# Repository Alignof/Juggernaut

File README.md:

# Juggernaut

Juggernaut は与えられた回路図とプログラムを読み解き，規定内の操作を行うことで時限爆弾型の「装置」を停止させる（解除する）競技です．
解除すべき「装置」とその回路図，書き込まれているプログラムが渡され，その内容を読み解きながらワイヤを切ったりボタンを押したり傾けたりして時間内に「装置」を停止させることを目指します．

作問者には回路構成力とプログラムを柔軟に書く力が，解除する側には回路図やデータシートを読む力とプログラムを素早く間違いなく解読する力が求められ，教育面での効果が期待できます．  
解除するまでの時間を競う競技型や，お互いに装置を作って解除しあってワイワイするイベント型を想定しています．

## 競技規則

[regulation.md](https://github.com/Alignof/Juggernaut/blob/master/regulation.md)を参照．

## 関連リポジトリ

運営などに便利なツールを用意しました．

### [Juggernaut_typst](https://github.com/Alignof/Juggernaut_typst)

運営に提出する仕様書（giver から solver に渡される問題文兼取説）の typst 版テンプレートです．

## 開催履歴

- 2020/12/19: SECCON2020 Contest of Contest 発表
- 2021/10/16: 第1回 SECCONCON 「Juggernaut #000」
- 2023/12/23: Juggernaut #001 @浅草橋ヒューリックホール
- 2024/09/14: Juggernaut #002 @Deep Tech CORE SAPPORO
- 2025/11/12-13: International Cybersecurity Challenge 小中学生向けワークショップ

## Author

2020 10.31  
Norimasa TAKANA  
Homepage: [https://n.takana.dev/](https://n.takana.dev/)  
Github : [https://github.com/Alignof/](https://github.com/Alignof/)  
Twitter : [https://twitter.com/\_Alignof](https://twitter.com/_Alignof)

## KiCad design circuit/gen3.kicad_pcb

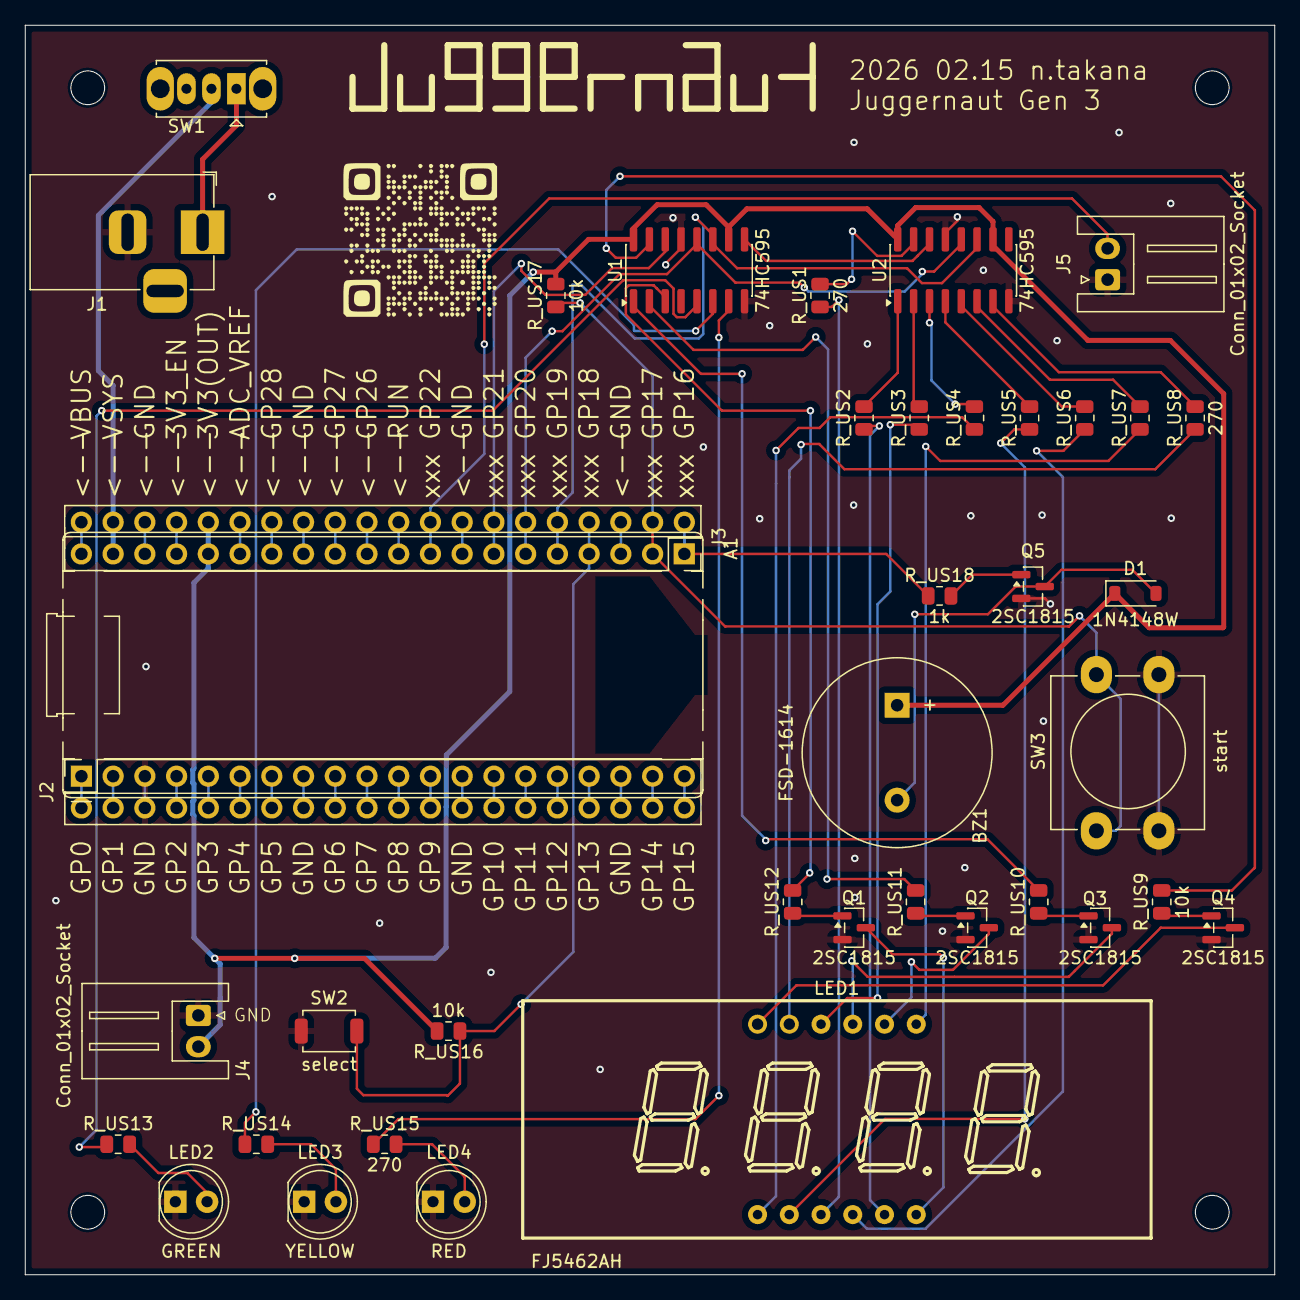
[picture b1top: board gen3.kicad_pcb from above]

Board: 2 copper layers, 100.0 x 100.0 mm, 44 parts (0 on the bottom side), 78 nets.

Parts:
A1: RaspberryPi_Pico; RaspberryPi_Pico_Common_THT
BZ1: FSD-1614; Buzzer_15x7.5RM7.6
D1: 1N4148W; D_SOD-123
H1, H2, H3, H4: MountingHole; MountingHole_2.7mm_M2.5
J1: Jack-DC; BarrelJack_Horizontal
J2: Conn_02x20_Row_Letter_Last; PinSocket_2x20_P2.54mm_1a-20a
J3: Conn_02x20_Row_Letter_Last; PinSocket_2x20_P2.54mm_20a_40a
J4, J5: Conn_01x02_Socket; JST_XH_S2B-XH-A_1x02_P2.50mm_Horizontal
LED1: FJ5462AH
LED2: GREEN; LED_D5.0mm
LED3: YELLOW; LED_D5.0mm
LED4: RED; LED_D5.0mm
Q1, Q2, Q3, Q4, Q5: 2SC1815; SOT-23
R_US1, R_US2, R_US3, R_US4, R_US5, R_US6, R_US7, R_US8, R_US13, R_US14, R_US15: 270; R_0805_2012Metric
R_US9, R_US10, R_US11, R_US12, R_US16, R_US17: 10k; R_0805_2012Metric
R_US18: 1k; R_0805_2012Metric
SW1: SW_Wuerth_450301014042; SW_Slide_SPDT_Straight_CK_OS102011MS2Q
SW2: select; SW_SPST_TS-1088-xR020
SW3: start; SW_PUSH-12mm_Wuerth-430476085716
U1, U2: 74HC595; SOIC-16_3.9x9.9mm_P1.27mm

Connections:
+3V3: BZ1.1 (-), D1.1 (K), J3.36a, J3.36b, J4.2, R_US16.2, R_US17.2, U1.10 (~SRCLR), U1.16 (VCC), U2.10 (~SRCLR), U2.16 (VCC)
/7seg_led/A: LED1.11 (A), R_US8.1
/7seg_led/B: LED1.7 (B), R_US7.1
/7seg_led/C: LED1.4 (C), R_US6.1
/7seg_led/D: LED1.2 (D), R_US5.1
/7seg_led/DIG1: LED1.12 (DIG1), Q4.3 (C)
/7seg_led/DIG2: LED1.9 (DIG2), Q3.3 (C)
/7seg_led/DIG3: LED1.8 (DIG3), Q2.3 (C)
/7seg_led/DIG4: LED1.6 (DIG4), Q1.3 (C)
/7seg_led/DP: LED1.3 (DP), R_US1.1
/7seg_led/E: LED1.1 (E), R_US4.1
/7seg_led/F: LED1.10 (F), R_US3.1
/7seg_led/G: LED1.5 (G), R_US2.1
/Pin1: J2.1a, J2.1b
/Pin2: J2.2a, J2.2b
/Pin4: J2.4a, J2.4b
/Pin5: J2.5a, J2.5b
/Pin6: J2.6a, J2.6b
/Pin7: J2.7a, J2.7b
/Pin8: J2.8a, J2.8b
/Pin9: J2.9a, J2.9b
/Pin10: J2.10a, J2.10b
/Pin11: J2.11a, J2.11b
/Pin12: J2.12a, J2.12b
/Pin13: J2.13a, J2.13b
/Pin14: J2.14a, J2.14b
/Pin15: J2.15a, J2.15b
/Pin16: J2.16a, J2.16b
/Pin17: J2.17a, J2.17b
/Pin18: J2.18a, J2.18b
/Pin19: J2.19a, J2.19b
/Pin20: J2.20a (Pin_none_a), J2.20b (Pin_none_b)
/Pin21: J3.21a, J3.21b, R_US18.1
/Pin22: J3.22a, J3.22b, R_US17.1, SW3.1
/Pin23: J3.23a, J3.23b
/Pin24: J3.24a, J3.24b, R_US16.1, SW2.2
/Pin25: J3.25a, J3.25b, U1.11 (SRCLK), U2.11 (SRCLK)
/Pin26: J3.26a, J3.26b, U1.12 (RCLK), U2.12 (RCLK)
/Pin27: J3.27a, J3.27b, U1.14 (SER)
/Pin28: J3.28a, J3.28b
/Pin29: J3.29a, J3.29b, J5.2
/Pin30: J3.30a, J3.30b
/Pin31: J3.31a, J3.31b
/Pin32: J3.32a, J3.32b
/Pin33: J3.33a, J3.33b
/Pin34: J3.34a, J3.34b
/Pin35: J3.35a, J3.35b
/Pin37: J3.37a, J3.37b
/Pin38: J3.38a, J3.38b
/Pin39: J3.39a, J3.39b, SW1.2 (C)
/Pin40: J3.40a, J3.40b
GNDPWR: J1.2, J2.3a, J2.3b, J4.1, J5.1, LED2.1 (K), LED3.1 (K), LED4.1 (K), Q1.2 (E), Q2.2 (E), Q3.2 (E), Q4.2 (E), Q5.2 (E), SW2.1, SW3.2, U1.8 (GND), U1.13 (~OE), U2.8 (GND), U2.13 (~OE)
unnamed: BZ1.2 (+), D1.2 (A), Q5.3 (C)
unnamed: LED2.2 (A), R_US13.2
unnamed: LED3.2 (A), R_US14.2
unnamed: LED4.2 (A), R_US15.2
unnamed: Q1.1 (B), R_US12.1
unnamed: Q2.1 (B), R_US11.1
unnamed: Q3.1 (B), R_US10.1
unnamed: Q4.1 (B), R_US9.1
unnamed: Q5.1 (B), R_US18.2
unnamed: J1.1, SW1.1 (B)
unnamed: R_US9.2, U1.15 (QA)
unnamed: R_US10.2, U1.1 (QB)
unnamed: R_US11.2, U1.2 (QC)
unnamed: R_US12.2, U1.3 (QD)
unnamed: R_US13.1, U1.5 (QF)
unnamed: R_US14.1, U1.6 (QG)
unnamed: U1.9 (QH'), U2.14 (SER)
unnamed: R_US15.1, U1.7 (QH)
unnamed: R_US1.2, U2.15 (QA)
unnamed: R_US2.2, U2.1 (QB)
unnamed: R_US3.2, U2.2 (QC)
unnamed: R_US4.2, U2.3 (QD)
unnamed: R_US5.2, U2.4 (QE)
unnamed: R_US6.2, U2.5 (QF)
unnamed: R_US7.2, U2.6 (QG)
unnamed: R_US8.2, U2.7 (QH)

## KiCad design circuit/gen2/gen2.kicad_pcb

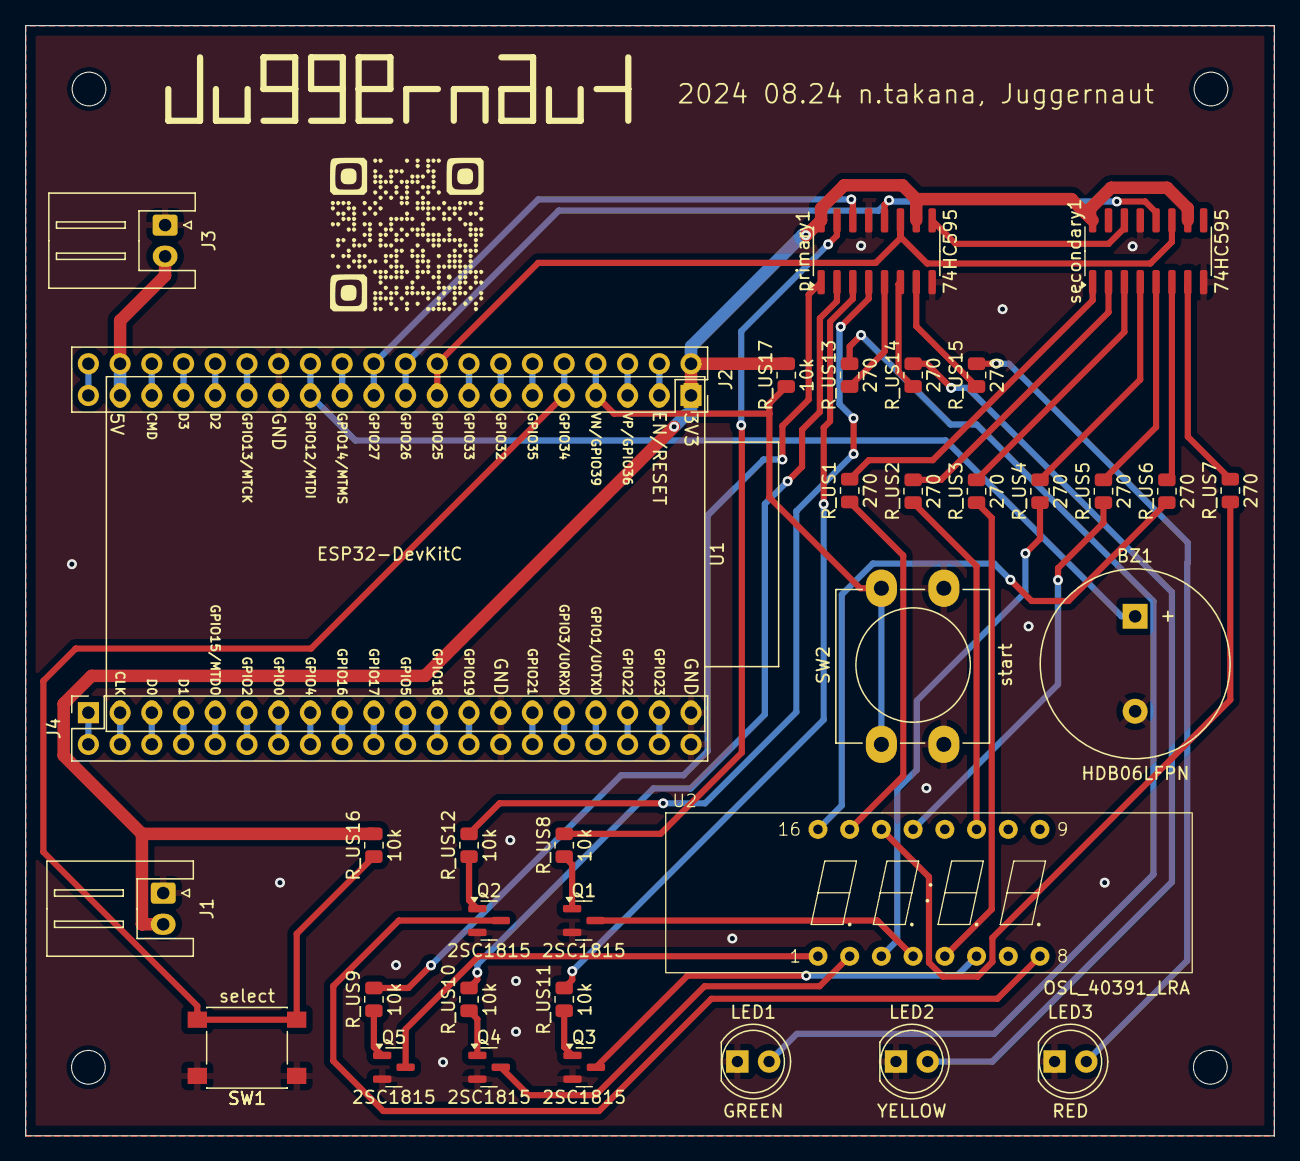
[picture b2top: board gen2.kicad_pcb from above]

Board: 2 copper layers, 100.0 x 88.9 mm, 40 parts (0 on the bottom side), 72 nets.

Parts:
BZ1: HDB06LFPN; Buzzer_15x7.5RM7.6
J1, J3: Conn_01x02_Socket; JST_XH_S2B-XH-A_1x02_P2.50mm_Horizontal
J2: Conn_02x20_Row_Letter_Last; PinSocket_2x20_P2.54mm_1a-19a
J4: Conn_02x20_Row_Letter_Last; PinSocket_2x20_P2.54mm_20a_38a
LED1: GREEN; LED_D5.0mm
LED2: YELLOW; LED_D5.0mm
LED3: RED; LED_D5.0mm
Q1, Q2, Q3, Q4, Q5: 2SC1815; SOT-23
R_US1, R_US2, R_US3, R_US4, R_US5, R_US6, R_US7, R_US13, R_US14, R_US15: 270; R_0805_2012Metric
R_US8, R_US9, R_US10, R_US11, R_US12, R_US16, R_US17: 10k; R_0805_2012Metric
SW1: select; SW_SPST_PTS645
SW2: start; SW_PUSH-12mm_Wuerth-430476085716
U1: ESP32-DevKitC
U2: OSL_40391_LRA
hole_lower_left: MountingHole_2.7mm_M2.5
hole_lower_right: MountingHole_2.7mm_M2.5
hole_upper_left: MountingHole_2.7mm_M2.5
hole_upper_right: MountingHole_2.7mm_M2.5
primary1: 74HC595; SOIC-16_3.9x9.9mm_P1.27mm
secondary1: 74HC595; SOIC-16_3.9x9.9mm_P1.27mm

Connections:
+3V3: J1.2, J2.1a, J2.1b, R_US16.2, R_US17.2, U1.1 (3V3), primary1.10 (~SRCLR), primary1.16 (VCC), secondary1.10 (~SRCLR), secondary1.16 (VCC)
+5V: J2.19a, J2.19b, J3.2, U1.19 (5V)
/Pin2: J2.2a, J2.2b, U1.2 (CHIP_PU)
/Pin3: J2.3a, J2.3b, U1.3 (SENSOR_VP/GPIO36/ADC1_CH0)
/Pin4: J2.4a, J2.4b, R_US17.1, SW2.1, U1.4 (SENSOR_VN/GPIO39/ADC1_CH3)
/Pin5: J2.5a, J2.5b, R_US16.1, SW1.2, U1.5 (VDET_1/GPIO34/ADC1_CH6)
/Pin6: J2.6a, J2.6b, U1.6 (VDET_2/GPIO35/ADC1_CH7)
/Pin7: J2.7a, J2.7b, U1.7 (32K_XP/GPIO32/ADC1_CH4)
/Pin8: J2.8a, J2.8b, U1.8 (32K_XN/GPIO33/ADC1_CH5)
/Pin9: J2.9a, J2.9b, U1.9 (DAC_1/ADC2_CH8/GPIO25), primary1.11 (SRCLK), secondary1.11 (SRCLK)
/Pin10: J2.10a, J2.10b, U1.10 (DAC_2/ADC2_CH9/GPIO26), primary1.12 (RCLK), secondary1.12 (RCLK)
/Pin11: J2.11a, J2.11b, U1.11 (ADC2_CH7/GPIO27), primary1.14 (SER)
/Pin12: J2.12a, J2.12b, U1.12 (MTMS/GPIO14/ADC2_CH6)
/Pin13: BZ1.1 (-), J2.13a, J2.13b, U1.13 (MTDI/GPIO12/ADC2_CH5)
/Pin15: J2.15a, J2.15b, U1.15 (MTCK/GPIO13/ADC2_CH4)
/Pin16: J2.16a, J2.16b, U1.16 (SD_DATA2/GPIO9)
/Pin17: J2.17a, J2.17b, U1.17 (SD_DATA3/GPIO10)
/Pin18: J2.18a, J2.18b, U1.18 (CMD)
/Pin20: J4.20a, J4.20b, U1.20 (SD_CLK/GPIO6)
/Pin21: J4.21a, J4.21b, U1.21 (SD_DATA0/GPIO7)
/Pin22: J4.22a, J4.22b, U1.22 (SD_DATA1/GPIO8)
/Pin23: J4.23a, J4.23b, U1.23 (MTDO/GPIO15/ADC2_CH3)
/Pin24: J4.24a, J4.24b, U1.24 (ADC2_CH2/GPIO2)
/Pin25: J4.25a, J4.25b, U1.25 (GPIO0/BOOT/ADC2_CH1)
/Pin26: J4.26a, J4.26b, U1.26 (ADC2_CH0/GPIO4)
/Pin27: J4.27a, J4.27b, U1.27 (GPIO16)
/Pin28: J4.28a, J4.28b, U1.28 (GPIO17)
/Pin29: J4.29a, J4.29b, U1.29 (GPIO5)
/Pin30: J4.30a, J4.30b, U1.30 (GPIO18)
/Pin31: J4.31a, J4.31b, U1.31 (GPIO19)
/Pin33: J4.33a, J4.33b, U1.33 (GPIO21)
/Pin34: J4.34a, J4.34b, U1.34 (U0RXD/GPIO3)
/Pin35: J4.35a, J4.35b, U1.35 (U0TXD/GPIO1)
/Pin36: J4.36a, J4.36b, U1.36 (GPIO22)
/Pin37: J4.37a, J4.37b, U1.37 (GPIO23)
GNDPWR: BZ1.2 (+), J1.1, J2.14a, J2.14b, J3.1, J4.32a, J4.32b, J4.38a, J4.38b, LED1.1 (K), LED2.1 (K), LED3.1 (K), Q1.2 (E), Q2.2 (E), Q3.2 (E), Q4.2 (E), Q5.2 (E), SW1.1, SW2.2, U1.14 (GND), U1.32 (GND), U1.38 (GND), primary1.8 (GND), primary1.13 (~OE), secondary1.8 (GND), secondary1.13 (~OE)
unnamed: LED1.2 (A), R_US13.2
unnamed: LED2.2 (A), R_US14.2
unnamed: LED3.2 (A), R_US15.2
unnamed: Q1.1 (B), R_US8.1
unnamed: Q1.3 (C), U2.4 (CC5)
unnamed: Q2.1 (B), R_US12.1
unnamed: Q2.3 (C), U2.8 (CC4)
unnamed: Q3.1 (B), R_US11.1
unnamed: Q3.3 (C), U2.6 (CC3)
unnamed: Q4.1 (B), R_US10.1
unnamed: Q4.3 (C), U2.2 (CC2)
unnamed: Q5.1 (B), R_US9.1
unnamed: Q5.3 (C), U2.1 (CC1)
unnamed: R_US7.1, U2.14 (a/D1)
unnamed: R_US6.1, U2.16 (b/D2)
unnamed: R_US5.1, U2.13 (c/D3)
unnamed: R_US4.1, U2.3 (d)
unnamed: R_US3.1, U2.5 (e)
unnamed: R_US2.1, U2.11 (f)
unnamed: R_US1.1, U2.15 (g)
unnamed: R_US8.2, primary1.15 (QA)
unnamed: R_US9.2, primary1.1 (QB)
unnamed: R_US10.2, primary1.2 (QC)
unnamed: R_US11.2, primary1.3 (QD)
unnamed: R_US12.2, primary1.4 (QE)
unnamed: R_US13.1, primary1.5 (QF)
unnamed: R_US14.1, primary1.6 (QG)
unnamed: primary1.9 (QH'), secondary1.14 (SER)
unnamed: R_US15.1, primary1.7 (QH)
unnamed: R_US1.2, secondary1.1 (QB)
unnamed: R_US2.2, secondary1.2 (QC)
unnamed: R_US3.2, secondary1.3 (QD)
unnamed: R_US4.2, secondary1.4 (QE)
unnamed: R_US5.2, secondary1.5 (QF)
unnamed: R_US6.2, secondary1.6 (QG)
unnamed: R_US7.2, secondary1.7 (QH)

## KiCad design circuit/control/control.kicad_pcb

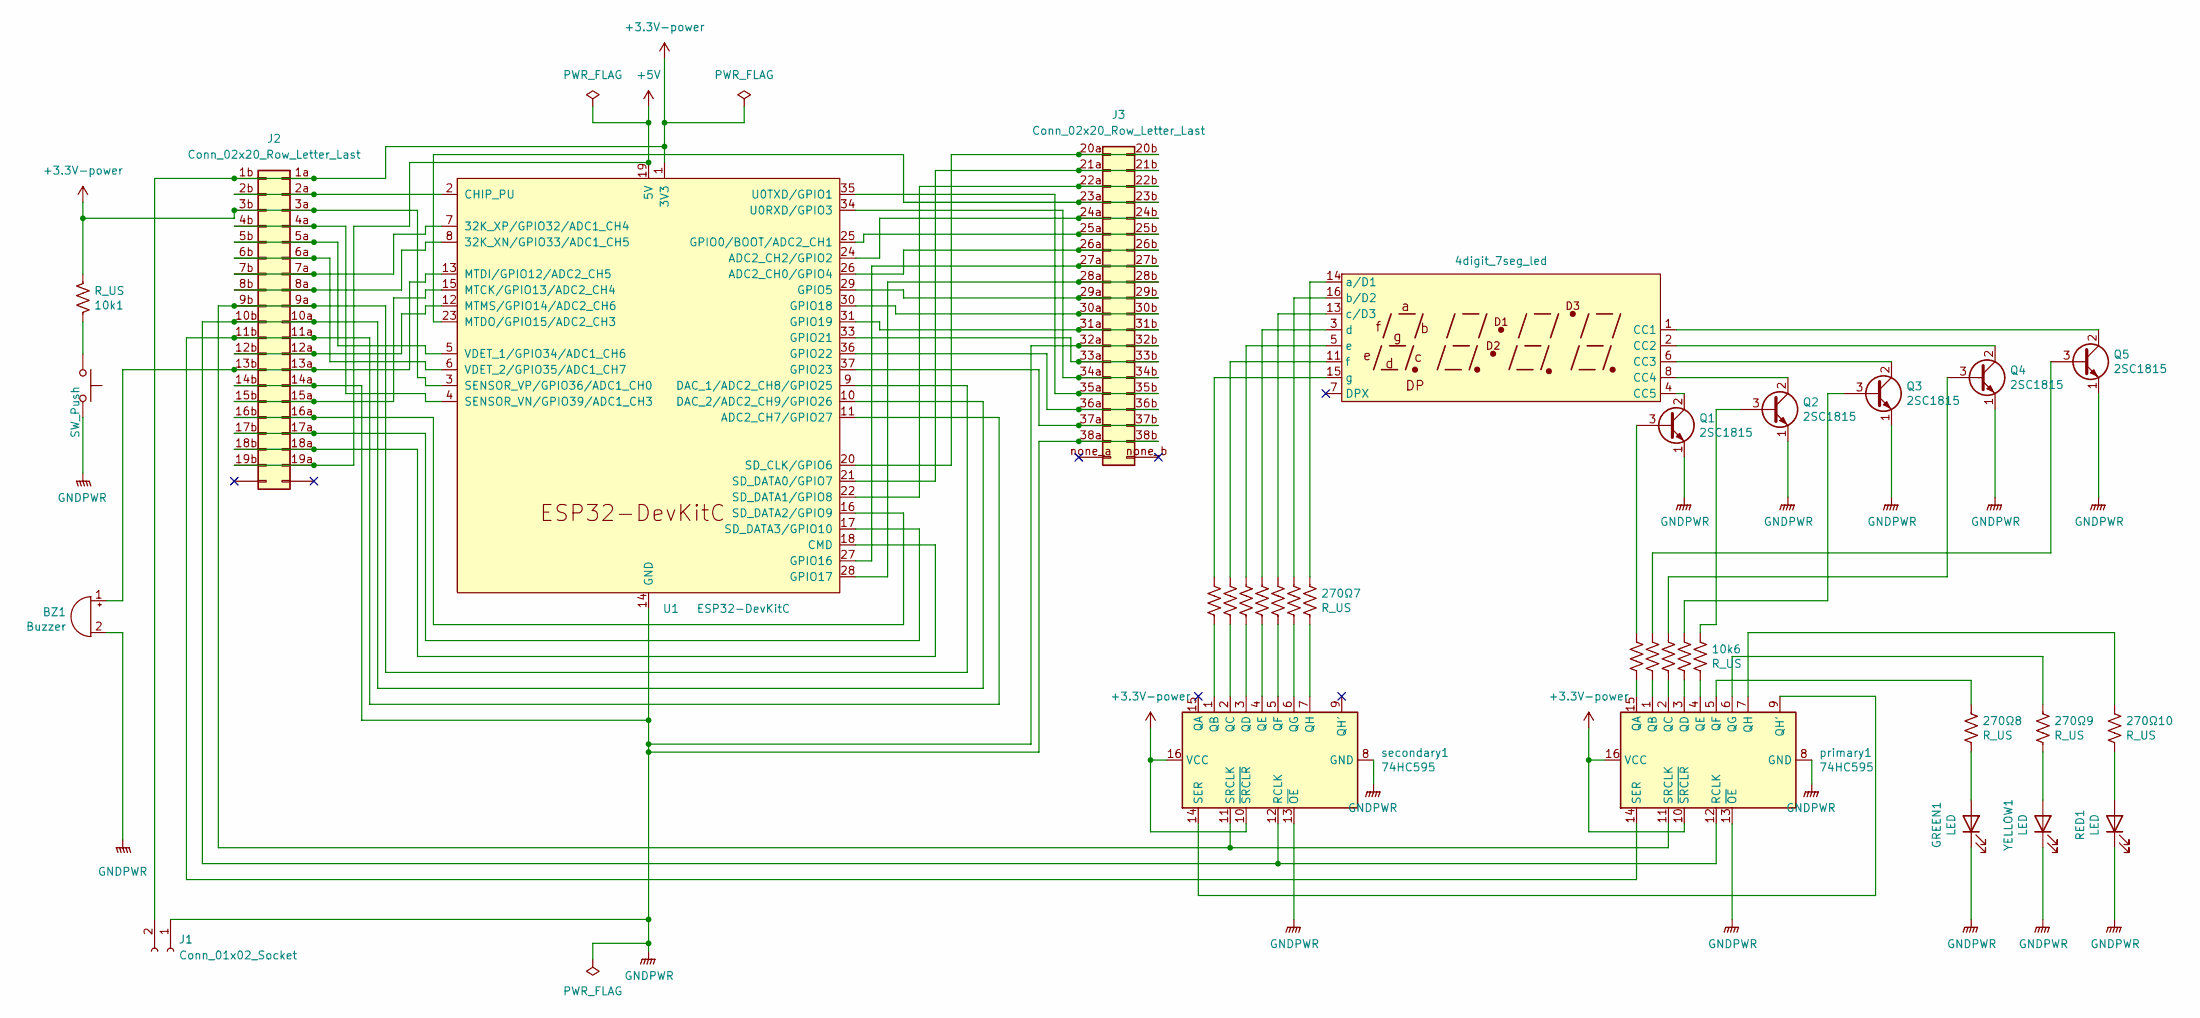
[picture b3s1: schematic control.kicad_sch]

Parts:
10k1, 10k2, 10k3, 10k4, 10k5, 10k6, 270Ω1, 270Ω2, 270Ω3, 270Ω4, 270Ω5, 270Ω6, 270Ω7, 270Ω8, 270Ω9, 270Ω10: R_US; R_Axial_DIN0207_L6.3mm_D2.5mm_P10.16mm_Horizontal
BZ1: Buzzer; Buzzer_15x7.5RM7.6
GREEN1: LED; LED_D1.8mm_W1.8mm_H2.4mm_Horizontal_O1.27mm_Z1.6mm
J1: Conn_01x02_Socket; PinHeader_1x02_P2.54mm_Vertical
J2: Conn_02x20_Row_Letter_Last; PinSocket_2x20_P2.54mm_1a-19a
J3: Conn_02x20_Row_Letter_Last; PinSocket_2x20_P2.54mm_20a_38a
Q1, Q2, Q3, Q4, Q5: 2SC1815; TO-92_Inline_Wide
RED1: LED; LED_D1.8mm_W1.8mm_H2.4mm_Horizontal_O1.27mm_Z1.6mm
SW1: SW_Push; SW_PUSH-12mm_Wuerth-430476085716
U1: ESP32-DevKitC
U2: 4digit_7seg_led; OSL_40391_LRA
YELLOW1: LED; LED_D1.8mm_W1.8mm_H2.4mm_Horizontal_O1.27mm_Z1.6mm
primary1: 74HC595; DIP-16_W7.62mm_Socket
secondary1: 74HC595; DIP-16_W7.62mm_Socket

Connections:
+3V3: 10k1.2, J1.2, J2.1a, J2.1b, J2.3a, J2.3b, U1.1 (3V3), U1.3 (SENSOR_VP/GPIO36/ADC1_CH0), primary1.10 (~SRCLR), primary1.16 (VCC), secondary1.10 (~SRCLR), secondary1.16 (VCC)
+5V: J2.19a, J2.19b, U1.19 (5V)
GNDPWR: BZ1.2 (+), GREEN1.1 (K), J1.1, J2.14a, J2.14b, J3.32a, J3.32b, J3.38a, J3.38b, Q1.1 (E), Q2.1 (E), Q3.1 (E), Q4.1 (E), Q5.1 (E), RED1.1 (K), SW1.1, U1.14 (GND), U1.32 (GND), U1.38 (GND), YELLOW1.1 (K), primary1.8 (GND), primary1.13 (~OE), secondary1.8 (GND), secondary1.13 (~OE); also elsewhere on the board
unnamed: 10k1.1, SW1.2
unnamed 4: BZ1.1 (-), J2.13a, J2.13b, U1.13 (MTDI/GPIO12/ADC2_CH5); also elsewhere on the board
unnamed: 270Ω8.2, GREEN1.2 (A)
unnamed: J2.2a, J2.2b, U1.2 (CHIP_PU)
unnamed: J2.4a, J2.4b, U1.4 (SENSOR_VN/GPIO39/ADC1_CH3)
unnamed: J2.5a, J2.5b, U1.5 (VDET_1/GPIO34/ADC1_CH6)
unnamed: J2.6a, J2.6b, U1.6 (VDET_2/GPIO35/ADC1_CH7)
unnamed: J2.7a, J2.7b, U1.7 (32K_XP/GPIO32/ADC1_CH4)
unnamed: J2.8a, J2.8b, U1.8 (32K_XN/GPIO33/ADC1_CH5)
unnamed: J2.9a, J2.9b, U1.9 (DAC_1/ADC2_CH8/GPIO25), primary1.11 (SRCLK), secondary1.11 (SRCLK)
unnamed: J2.10a, J2.10b, U1.10 (DAC_2/ADC2_CH9/GPIO26), primary1.12 (RCLK), secondary1.12 (RCLK)
unnamed: J2.11a, J2.11b, U1.11 (ADC2_CH7/GPIO27), primary1.14 (SER)
unnamed: J2.12a, J2.12b, U1.12 (MTMS/GPIO14/ADC2_CH6)
unnamed: J2.15a, J2.15b, U1.15 (MTCK/GPIO13/ADC2_CH4)
unnamed: J2.16a, J2.16b, U1.16 (SD_DATA2/GPIO9)
unnamed: J2.17a, J2.17b, U1.17 (SD_DATA3/GPIO10)
unnamed: J2.18a, J2.18b, U1.18 (CMD)
unnamed: J3.20a, J3.20b, U1.20 (SD_CLK/GPIO6)
unnamed: J3.21a, J3.21b, U1.21 (SD_DATA0/GPIO7)
unnamed: J3.22a, J3.22b, U1.22 (SD_DATA1/GPIO8)
unnamed: J3.23a, J3.23b, U1.23 (MTDO/GPIO15/ADC2_CH3)
unnamed: J3.24a, J3.24b, U1.24 (ADC2_CH2/GPIO2)
unnamed: J3.25a, J3.25b, U1.25 (GPIO0/BOOT/ADC2_CH1)
unnamed: J3.26a, J3.26b, U1.26 (ADC2_CH0/GPIO4)
unnamed: J3.27a, J3.27b, U1.27 (GPIO16)
unnamed: J3.28a, J3.28b, U1.28 (GPIO17)
unnamed: J3.29a, J3.29b, U1.29 (GPIO5)
unnamed: J3.30a, J3.30b, U1.30 (GPIO18)
unnamed: J3.31a, J3.31b, U1.31 (GPIO19)
unnamed: J3.33a, J3.33b, U1.33 (GPIO21)
unnamed: J3.34a, J3.34b, U1.34 (U0RXD/GPIO3)
unnamed: J3.35a, J3.35b, U1.35 (U0TXD/GPIO1)
unnamed: J3.36a, J3.36b, U1.36 (GPIO22)
unnamed: J3.37a, J3.37b, U1.37 (GPIO23)
unnamed: 10k2.1, Q1.3 (B)
unnamed: Q1.2 (C), U2.4 (CC5)
unnamed: 10k6.1, Q2.3 (B)
unnamed: Q2.2 (C), U2.8 (CC4)
unnamed: 10k5.1, Q3.3 (B)
unnamed: Q3.2 (C), U2.6 (CC3)
unnamed: 10k4.1, Q4.3 (B)
unnamed: Q4.2 (C), U2.2 (CC2)
unnamed: 10k3.1, Q5.3 (B)
unnamed: Q5.2 (C), U2.1 (CC1)
unnamed: 270Ω10.2, RED1.2 (A)
unnamed: 270Ω7.1, U2.14 (a/D1)
unnamed: 270Ω6.1, U2.16 (b/D2)
unnamed: 270Ω5.1, U2.13 (c/D3)
unnamed: 270Ω4.1, U2.3 (d)
unnamed: 270Ω3.1, U2.5 (e)
unnamed: 270Ω2.1, U2.11 (f)
unnamed: 270Ω1.1, U2.15 (g)
unnamed: 270Ω9.2, YELLOW1.2 (A)
unnamed: 10k2.2, primary1.15 (QA)
unnamed: 10k3.2, primary1.1 (QB)
unnamed: 10k4.2, primary1.2 (QC)
unnamed: 10k5.2, primary1.3 (QD)
unnamed: 10k6.2, primary1.4 (QE)
unnamed: 270Ω8.1, primary1.5 (QF)
unnamed: 270Ω9.1, primary1.6 (QG)
unnamed: primary1.9 (QH'), secondary1.14 (SER)
unnamed: 270Ω10.1, primary1.7 (QH)
unnamed: 270Ω1.2, secondary1.1 (QB)
unnamed: 270Ω2.2, secondary1.2 (QC)
unnamed: 270Ω3.2, secondary1.3 (QD)
unnamed: 270Ω4.2, secondary1.4 (QE)
unnamed: 270Ω5.2, secondary1.5 (QF)
unnamed: 270Ω6.2, secondary1.6 (QG)
unnamed: 270Ω7.2, secondary1.7 (QH)

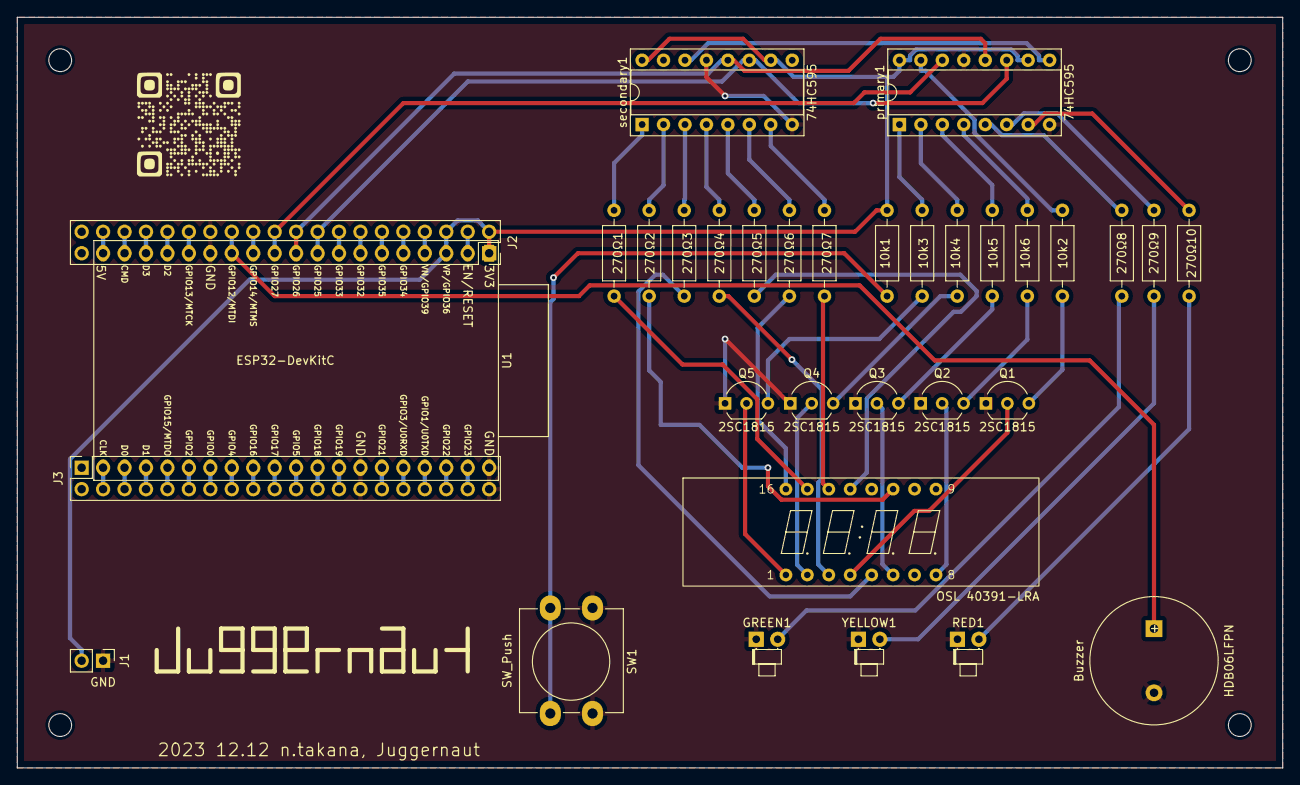
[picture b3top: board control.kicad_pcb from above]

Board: 2 copper layers, 149.9 x 88.9 mm, 37 parts (0 on the bottom side), 72 nets.

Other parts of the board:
HDB06LFPN: Buzzer; Buzzer_15x7.5RM7.6
hole_lower_left: MountingHole_2.7mm_M2.5
hole_lower_right: MountingHole_2.7mm_M2.5
hole_upper_left: MountingHole_2.7mm_M2.5
hole_upper_right: MountingHole_2.7mm_M2.5

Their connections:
GNDPWR: HDB06LFPN.2 (+); also elsewhere on the board
unnamed 4: HDB06LFPN.1 (-); also elsewhere on the board

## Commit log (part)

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2020-03-14 add readme
2020-10-25 edit README
2020-10-25 edit section B
2020-10-25 ver 0.0.2
2020-10-30 ver 0.0.3
2020-10-30 ver 0.0.4
2020-10-31 add image
2020-10-31 add pdf
2020-10-31 added example.ino
2020-12-15 [update] update twitter id
2020-12-17 [add] add src/Timer/Timer.ino
2020-12-18 [update] update .ino file
2020-12-18 [update] update function gaming
2020-12-19 [fix] remove description.pdf
2020-12-19 [update] update image
2020-12-19 [update] lotate image in README.md
2020-12-19 [fix] fix image in README.md
2021-07-18 [update] update the link
2021-08-23 [refactor] fix some indent and coding rule
2021-08-24 [add] add the circuit diagram
2021-08-25 [update] update the circuit diagram
2021-09-08 [update] update the pin assign of BUZZER (23 -> 14)
2021-09-08 [fix] remove the Serial communication
2021-09-09 [add] add the event info
2021-09-13 [update] update the BUZZER pin
2021-09-13 [update] update the cicuit diagram
2021-09-13 [update] add the delay to data_send() and 7seg LED displaying become stable
2021-09-15 [update] update the pin assign
2021-09-23 Create LICENSE
2021-09-28 [add] add the giver code space
2021-09-28 [add] add a function succeeded and failed
2021-10-01 [update] remove proposal.md
2021-10-03 [add] add required_tools.md
2021-10-04 [add] add the start/reset switch
2021-10-04 [update] update circuit diagram
2021-10-04 [fix] fix the value of resistance in circuit diagram
2021-10-04 [update] enable to stop the buzzer when push the start/reset switch
2021-10-05 [add] add the specification builder as a submodule
2021-10-06 [fix] fix the repository url
2021-10-07 [add] regulation.md
2021-10-07 [edit] edit README.md
2021-10-08 [update] move part of setting pin to giver code space
2023-11-18 [update] update the description
2023-12-11 [update] udpate kicad file
2023-12-12 [update] update circuit.png
2023-12-12 [add] add .gitignore
2023-12-12 [update] update control circuit
2023-12-12 [add] add logo.png
2023-12-12 [update] update README.md
2023-12-12 [fix] fix circuit image
2023-12-13 [update] update example code
2023-12-19 [update] rename src/ example_src
2023-12-20 [update] update control.ino
2023-12-22 [update] update regulation
2024-08-19 [update] update control
2024-08-19 [add] add control2
2024-08-23 [update] rename control to gen1
2024-08-23 [add] add gen1.5
2024-08-23 [add] add footprint data
2024-08-23 [wip][add] add gen2
2024-08-25 [update] ignroe autosave file
2024-08-25 [update] gen2 is production ready
2024-09-11 [update] gen2 ordered
2024-09-11 [add] modify to use timer interrupt
2024-09-11 [update] move updating `time_remain` to `onTimer`
2024-09-11 [update] update example problem
2024-09-11 [!][wip][update] move example_src/Timer to Example
2024-09-11 [add] add Example/red_or_blue2.ino
2024-09-11 [update] select challenge by the button
2025-09-01 [update] update top image
2026-02-03 [update] remove `Juggernaut_spec_builder`
2026-02-03 [!][update] move old generation's circuits and source codes to archive directory
2026-02-03 [update] update README
2026-02-04 [add] add flake.nix and rust-toolchain.toml
2026-02-04 [wip][add] init cargo project
2026-02-04 [add] divide shift register driver into display.rs
2026-02-14 [add] add circuit/
2026-02-14 [add] add DC jack
2026-02-14 [update] update buzzer peripheral circuit
2026-02-14 [add] add seven segment led library
2026-02-14 [update] update 7seg led peripheral circuit
2026-02-14 [update] re-annotate symbols
2026-02-14 [update] rename original pin socket library
2026-02-14 [add] import FJ5462AH from jlcpcb
2026-02-14 [fix] fix pin number of the pin socket footprint
2026-02-14 [update] ignore tmp files
2026-02-14 [wip][add] init pcb data
2026-02-14 [update] print pin number as footprint
2026-02-15 [update] add the regulation as footprint to back side
2026-02-15 [update] update layout to allocate enough connector placing space
2026-02-15 [add] add connector for detonator
2026-02-15 [add] add jlcpcb bom data
2026-02-15 [fix] update slide switch's footprint
2026-02-15 [wip][add] apply auto generated routing
2026-02-15 [add] add the GND zone
2026-02-15 [!][fix] fix routing 3v3 signal
2026-02-15 [update] increase GND track width
2026-03-02 [add] generated produciton files
